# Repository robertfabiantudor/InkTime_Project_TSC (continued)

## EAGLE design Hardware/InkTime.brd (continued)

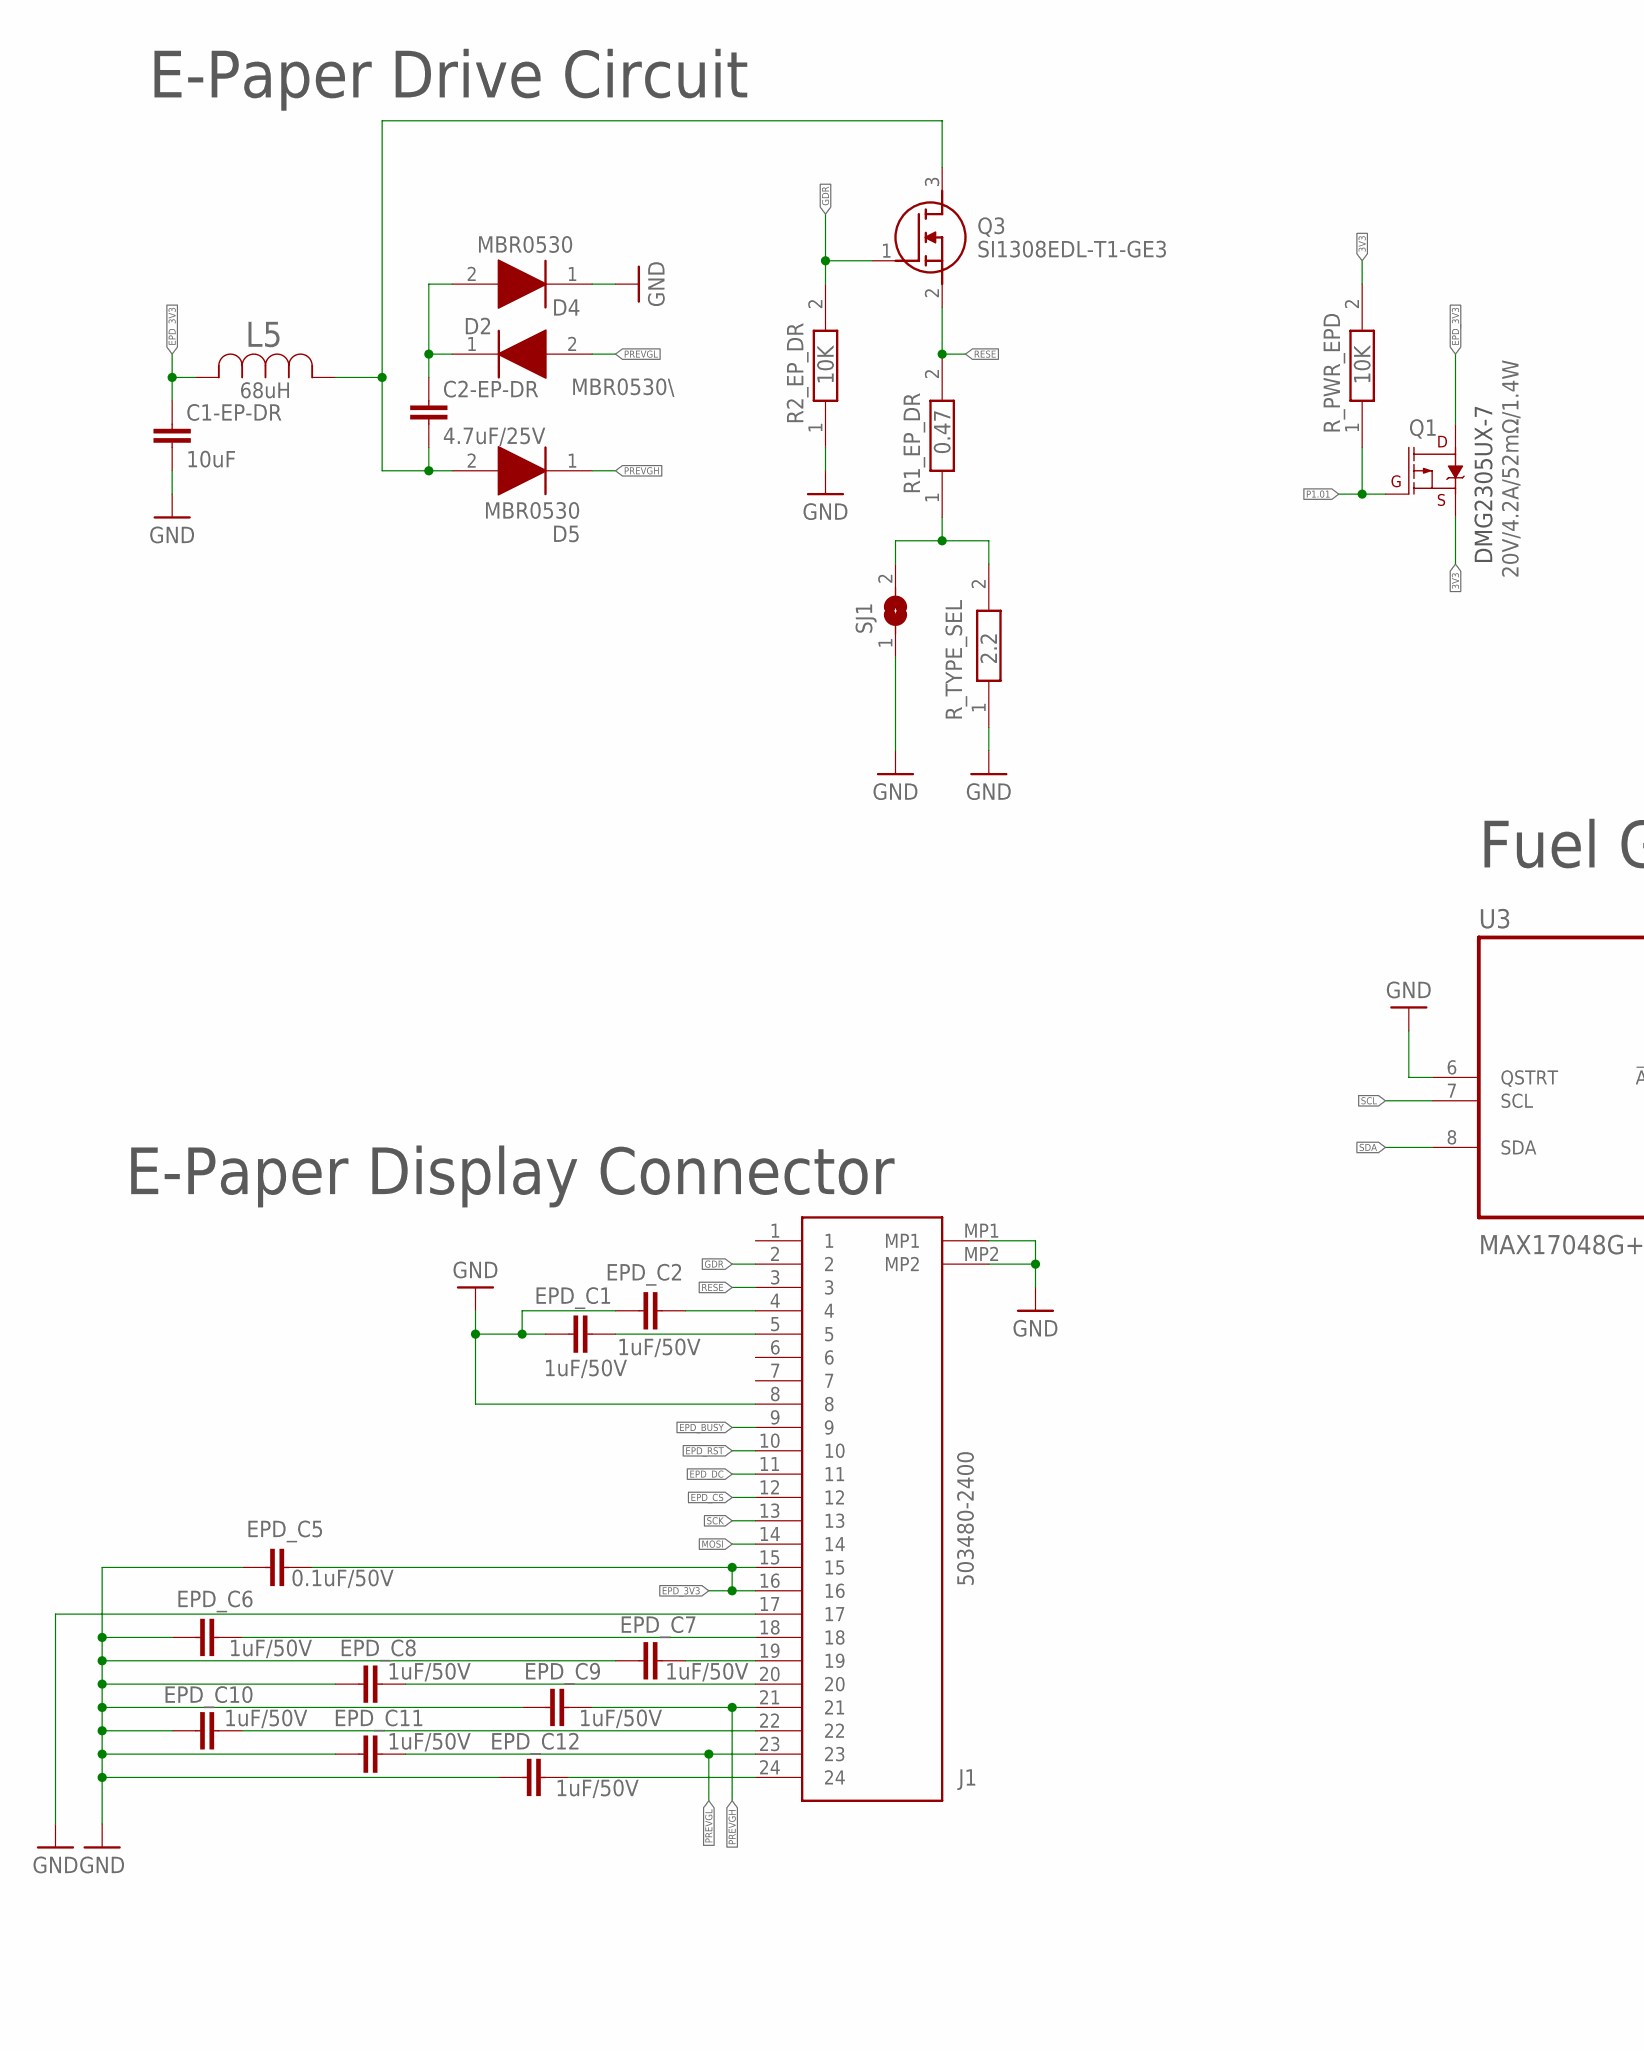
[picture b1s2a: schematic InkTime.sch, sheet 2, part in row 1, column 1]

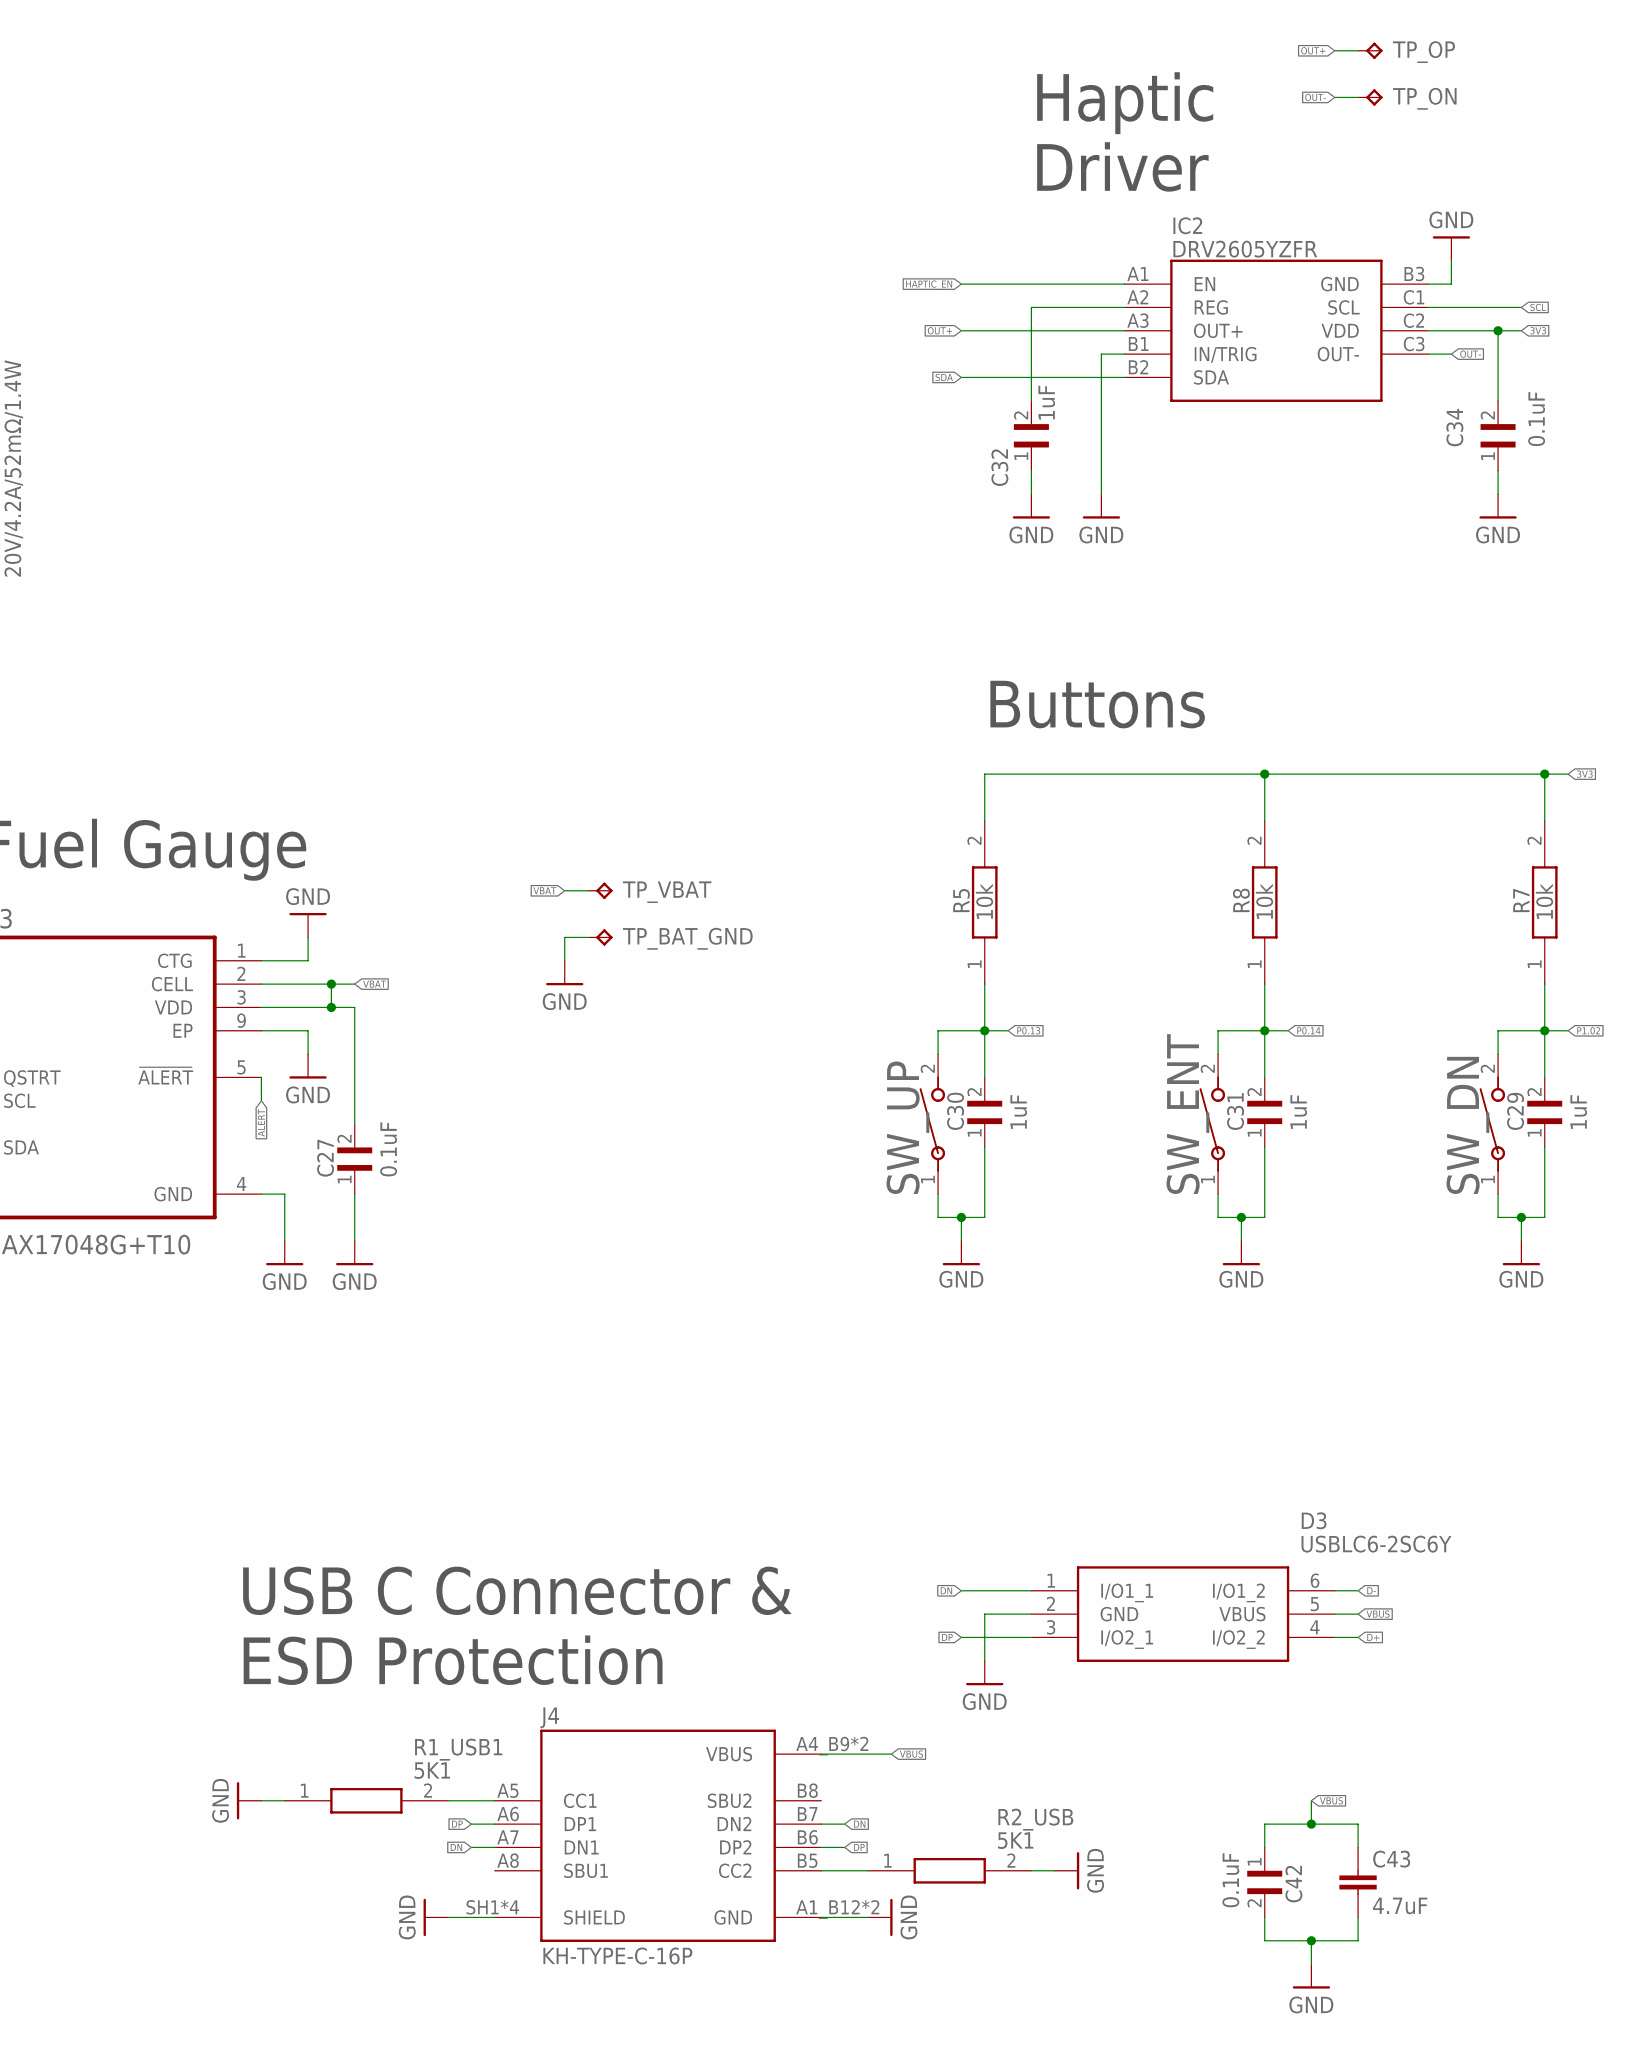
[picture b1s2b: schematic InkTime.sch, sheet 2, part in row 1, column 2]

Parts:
C1-EP-DR: 10uF; NORDIC_NRF_3_RESC0402_L
C2-EP-DR: 4.7uF/25V; NORDIC_NRF_3_RESC0402_L
C27, C34, C42: 0.1uF; GRM011R60J152KE01L_1_0201
C29, C30, C31, C32: 1uF; GRM011R60J152KE01L_1_0201
C43: 4.7uF; NORDIC_NRF_3_RESC0402_L
D2: MBR0530\; ESP32_C6_LIBRARY_5_SOD3716X135N
D3: USBLC6-2SC6Y; ESP32_C6_LIBRARY_3_SOT95P280X145-6N
D4, D5: MBR0530; ESP32_C6_LIBRARY_5_SOD3716X135N
EPD_C1, EPD_C2, EPD_C6, EPD_C7, EPD_C8, EPD_C9, EPD_C10, EPD_C11, EPD_C12: 1uF/50V; NORDIC_NRF_3_RESC0402_L
EPD_C5: 0.1uF/50V; NORDIC_NRF_3_RESC0201_L
IC2: DRV2605YZFR; DRV2605YZFR_BGA9C50P3X3_144X144X62
J1: 503480-2400; 503480-2400_5034802400
J4: KH-TYPE-C-16P; KH-TYPE-C-16P_KINGHELM_KH-TYPE-C-16P
L5: 68uH; ESP32_C6_LIBRARY_2_IND_4828-WE-TPC_WRE
Q1: 20V/4.2A/52mΩ/1.4W; ESP32_C6_LIBRARY_4_ESP32_C6_LIBRARY_4_ESP32_C6_LIBRARY_4_ES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
Q3: SI1308EDL-T1-GE3; ESP32_C6_LIBRARY_6_SOT65P210X110-3N
R1_EP_DR: 0.47; CPF0201D7K68C1_0201
R1_USB1, R2_USB: 5K1; CPF0201D7K68C1_0201
R2_EP_DR: 10K; CPF0201D7K68C1_0201
R5, R7, R8: 10k; CPF0201D7K68C1_0201
R_PWR_EPD: 10K; CPF0201D7K68C1_0201
R_TYPE_SEL: 2.2; CPF0201D7K68C1_0201
SJ1: ESP32_C6_LIBRARY_7_JUMPER_SJ
SW_DN: 2025-10-22_07-23-44_LIBRARY_EVP-AKE31ASW_EVP-AKE3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; 2025-10-22_07-23-44_LIBRARY_SW_EVP-AKE31A_PAN
SW_ENT: 2025-10-22_07-23-44_LIBRARY_EVP-AKE31ASW_EVP-AKE3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; 2025-10-22_07-23-44_LIBRARY_SW_EVP-AKE31A_PAN
SW_UP: 2025-10-22_07-23-44_LIBRARY_EVP-AKE31ASW_EVP-AKE3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; 2025-10-22_07-23-44_LIBRARY_SW_EVP-AKE31A_PAN
TP_BAT_GND: HECTOR_WATCH_1_TPTP20R; HECTOR_WATCH_1_TP20R
TP_ON: HECTOR_WATCH_1_TPTP20R; HECTOR_WATCH_1_TP20R
TP_OP: HECTOR_WATCH_1_TPTP20R; HECTOR_WATCH_1_TP20R
TP_VBAT: HECTOR_WATCH_1_TPTP20R; HECTOR_WATCH_1_TP20R
U3: MAX17048G+T10; ESP32_C6_LIBRARY_SON50P200X200X80-9N

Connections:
3V3: C34.2, IC2.C2 (VDD), Q1.2 (S), R5.2, R7.2, R8.2, R_PWR_EPD.2; also elsewhere on the board
ALERT: U3.5 (!ALERT); also elsewhere on the board
D+: D3.4 (I/O2_2); also elsewhere on the board
D-: D3.6 (I/O1_2); also elsewhere on the board
DN: D3.1 (I/O1_1), J4.A7 (DN1), J4.B7 (DN2)
DP: D3.3 (I/O2_1), J4.A6 (DP1), J4.B6 (DP2)
EPD_3V3: C1-EP-DR.2, EPD_C5.2, J1.15, J1.16, L5.2, Q1.3 (D)
EPD_BUSY: J1.9; also elsewhere on the board
EPD_CS: J1.12; also elsewhere on the board
EPD_DC: J1.11; also elsewhere on the board
EPD_RST: J1.10; also elsewhere on the board
GDR: J1.2, Q3.1 (G), R2_EP_DR.2
GND: C1-EP-DR.1, C27.1, C29.1, C30.1, C31.1, C32.1, C34.1, C42.2, C43.2, D3.2 (GND), D4.1 (K), EPD_C1.1, EPD_C2.1, EPD_C5.1, EPD_C6.1, EPD_C7.1, EPD_C8.1, EPD_C9.1, EPD_C10.1, EPD_C11.1, EPD_C12.1, IC2.B1 (IN/TRIG), IC2.B3 (GND), J1.8, J1.17, J1.MP1, J1.MP2, J4.A1_B12 (GND), J4.A12_B1 (GND), J4.SH1 (SHIELD), J4.SH2 (SHIELD), J4.SH3 (SHIELD), J4.SH4 (SHIELD), R1_USB1.1, R2_EP_DR.1, R2_USB.2, R_TYPE_SEL.1, SJ1.1, SW_DN.1, SW_ENT.1, SW_UP.1, TP_BAT_GND.TP, U3.1 (CTG), U3.4 (GND), U3.6 (QSTRT), U3.9 (EP); also elsewhere on the board
HAPTIC_EN: IC2.A1 (EN); also elsewhere on the board
MOSI: J1.14; also elsewhere on the board
unnamed: C32.2, IC2.A2 (REG)
unnamed: J4.B5 (CC2), R2_USB.1
unnamed: J4.A5 (CC1), R1_USB1.2
unnamed: EPD_C2.2, J1.4
unnamed: EPD_C6.2, J1.18
unnamed: EPD_C1.2, J1.5
unnamed: EPD_C7.2, J1.19
unnamed: EPD_C8.2, J1.20
unnamed: EPD_C10.2, J1.22
unnamed: EPD_C12.2, J1.24
unnamed: C2-EP-DR.1, D5.2 (A), L5.1, Q3.3 (D)
unnamed: R1_EP_DR.1, R_TYPE_SEL.2, SJ1.2
unnamed: C2-EP-DR.2, D2.1 (K), D4.2 (A)
OUT+: IC2.A3 (OUT+), TP_OP.TP
OUT-: IC2.C3 (OUT-), TP_ON.TP
P0.13: C30.2, R5.1, SW_UP.2; also elsewhere on the board
P0.14: C31.2, R8.1, SW_ENT.2; also elsewhere on the board
P1.01: Q1.1 (G), R_PWR_EPD.1; also elsewhere on the board
P1.02: C29.2, R7.1, SW_DN.2; also elsewhere on the board
PREVGH: D5.1 (K), EPD_C9.2, J1.21
PREVGL: D2.2 (A), EPD_C11.2, J1.23
RESE: J1.3, Q3.2 (S), R1_EP_DR.2
SCK: J1.13; also elsewhere on the board
SCL: IC2.C1 (SCL), U3.7 (SCL); also elsewhere on the board
SDA: IC2.B2 (SDA), U3.8 (SDA); also elsewhere on the board
VBAT: C27.2, TP_VBAT.TP, U3.2 (CELL), U3.3 (VDD); also elsewhere on the board
VBUS: C42.1, C43.1, D3.5 (VBUS), J4.A4_B9 (VBUS), J4.A9_B4 (VBUS); also elsewhere on the board

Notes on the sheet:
Haptic Driver
Buttons
Fuel Gauge
USB C Connector & ESD Protection
E-Paper Display Connector
E-Paper Drive Circuit
DMG2305UX-7

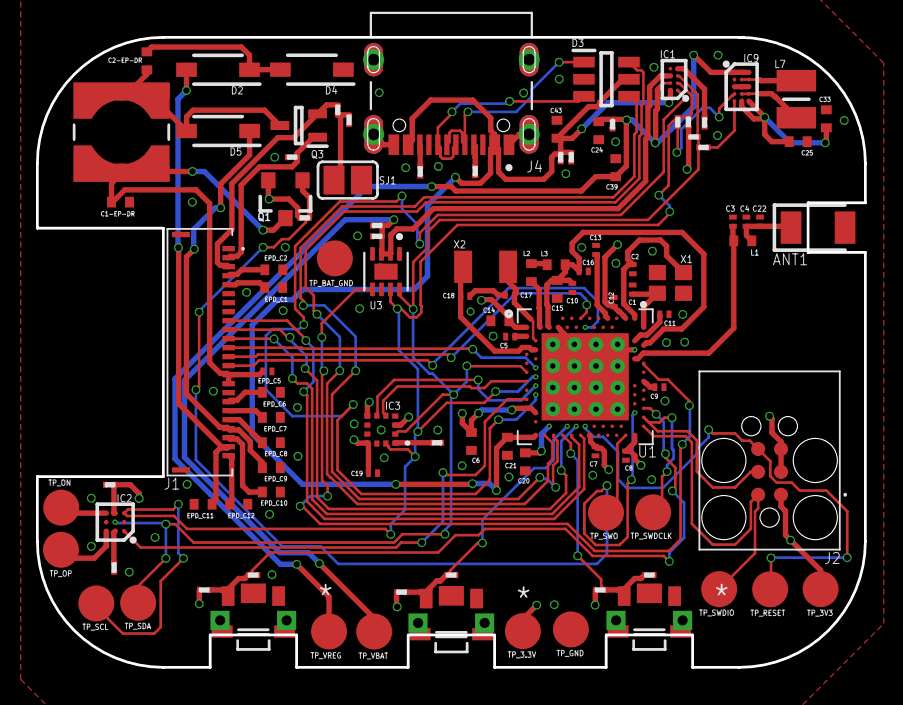
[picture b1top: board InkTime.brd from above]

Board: 4 copper layers, 46.0 x 35.0 mm, 105 parts (0 on the bottom side), 70 nets.

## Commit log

2026-04-10 added Hardware and Manufacturing folders
2026-04-10 added Mechanical folder and Images
2026-04-10 added image
2026-04-18 added Assets folder
2026-04-18 Fixed issues and finished 3D Models
2026-04-18 Fixed problem with gif
2026-04-18 Rename gerbers.zip to Gerbers.zip
2026-04-20 Updated Bill of Materials
